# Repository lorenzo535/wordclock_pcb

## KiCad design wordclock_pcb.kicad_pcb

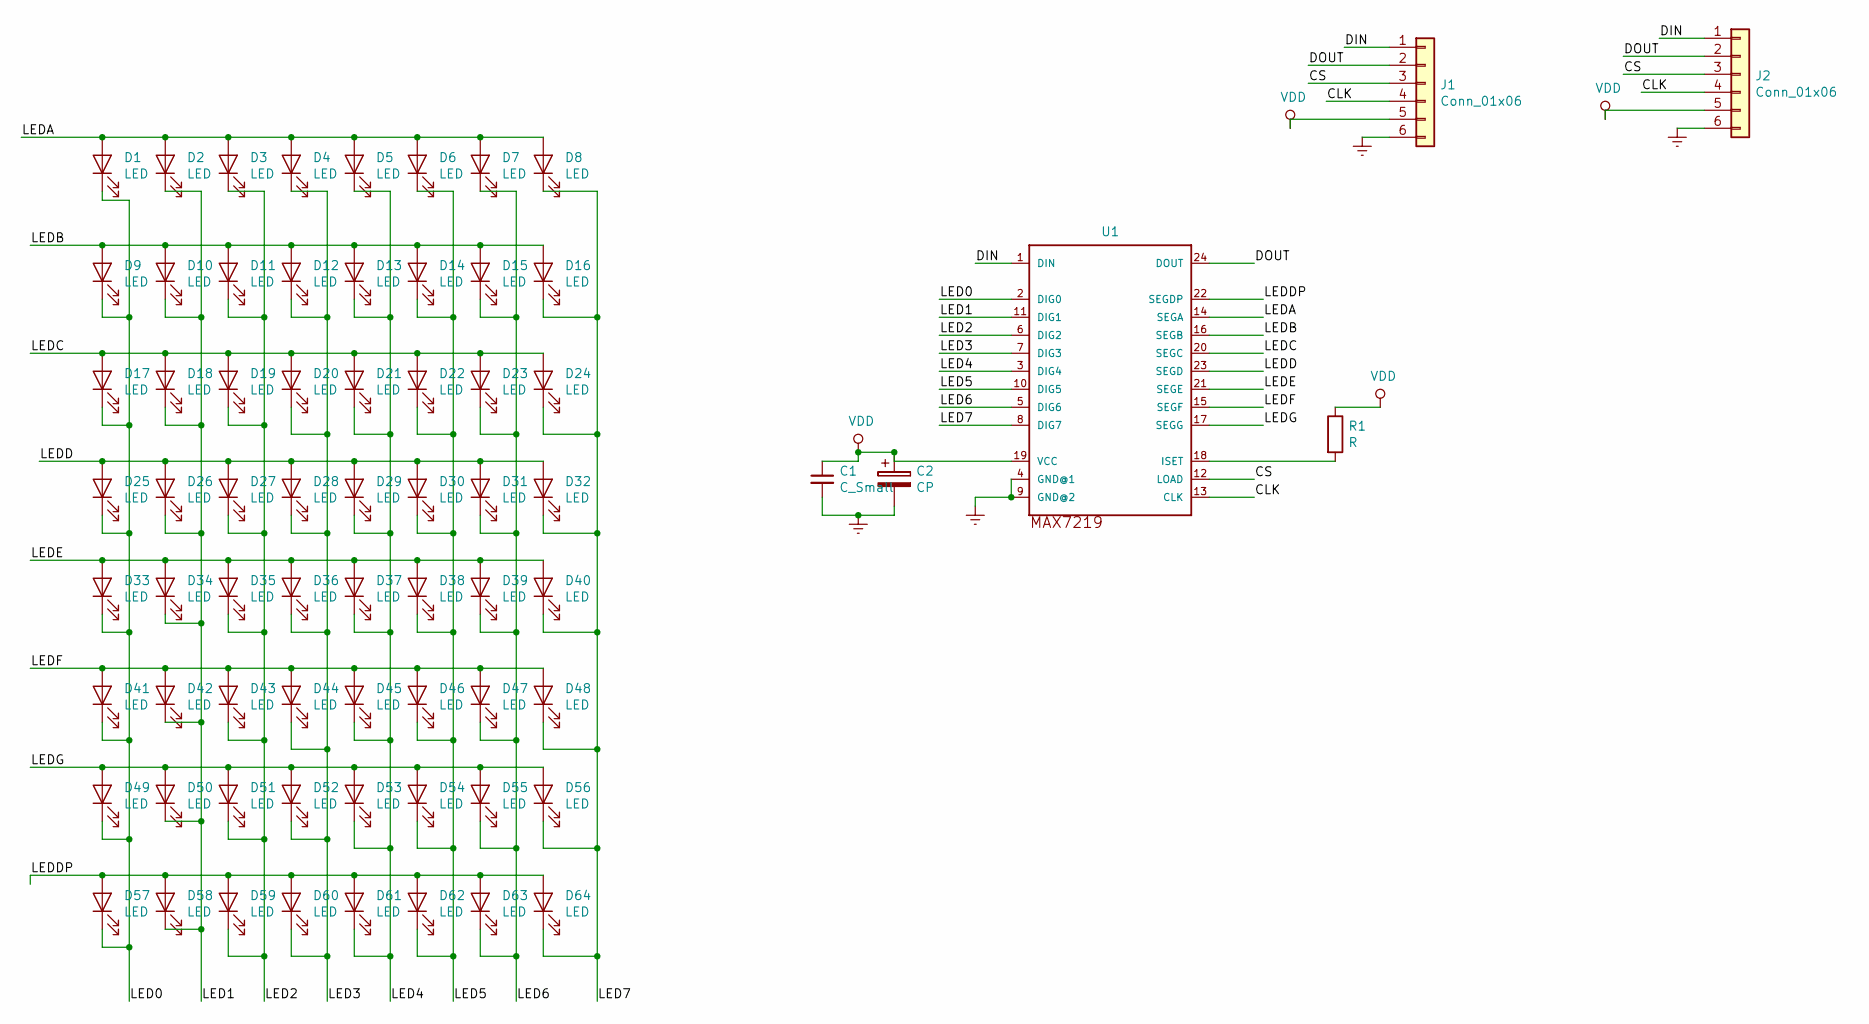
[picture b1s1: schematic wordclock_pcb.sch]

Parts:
C1: C_Small; CP_Radial_D4.0mm_P1.50mm
C2: CP; CP_Radial_D4.0mm_P1.50mm
D1, D2, D3, D4, D5, D6, D7, D8, D9, D10, D11, D12, D13, D14, D15, D16, D17, D18, D19, D20, D21, D22, D23, D24, D25, D26, D27, D28, D29, D30, D31, D32, D33, D34, D35, D36, D37, D38, D39, D40, D41, D42, D43, D44, D45, D46, D47, D48, D49, D50, D51, D52, D53, D54, D55, D56, D57, D58, D59, D60, D61, D62, D63, D64: LED; ledthroughhole
J1, J2: Conn_01x06; TerminalBlock_Phoenix_MPT-2.54mm_6pol
R1: R; R_Axial_DIN0207_L6.3mm_D2.5mm_P15.24mm_Horizontal
U1: MAX7219; DIL24

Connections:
/CLK: J1.4, J2.4, U1.13 (CLK)
/CS: J1.3, J2.3, U1.12 (LOAD)
/DIN: J1.1, J2.1, U1.1 (DIN)
/DOUT: J1.2, J2.2, U1.24 (DOUT)
/LED0: D1.1 (K), D9.1 (K), D17.1 (K), D25.1 (K), D33.1 (K), D41.1 (K), D49.1 (K), D57.1 (K), U1.2 (DIG0)
/LED1: D2.1 (K), D10.1 (K), D18.1 (K), D26.1 (K), D34.1 (K), D42.1 (K), D50.1 (K), D58.1 (K), U1.11 (DIG1)
/LED2: D3.1 (K), D11.1 (K), D19.1 (K), D27.1 (K), D35.1 (K), D43.1 (K), D51.1 (K), D59.1 (K), U1.6 (DIG2)
/LED3: D4.1 (K), D12.1 (K), D20.1 (K), D28.1 (K), D36.1 (K), D44.1 (K), D52.1 (K), D60.1 (K), U1.7 (DIG3)
/LED4: D5.1 (K), D13.1 (K), D21.1 (K), D29.1 (K), D37.1 (K), D45.1 (K), D53.1 (K), D61.1 (K), U1.3 (DIG4)
/LED5: D6.1 (K), D14.1 (K), D22.1 (K), D30.1 (K), D38.1 (K), D46.1 (K), D54.1 (K), D62.1 (K), U1.10 (DIG5)
/LED6: D7.1 (K), D15.1 (K), D23.1 (K), D31.1 (K), D39.1 (K), D47.1 (K), D55.1 (K), D63.1 (K), U1.5 (DIG6)
/LED7: D8.1 (K), D16.1 (K), D24.1 (K), D32.1 (K), D40.1 (K), D48.1 (K), D56.1 (K), D64.1 (K), U1.8 (DIG7)
/LEDA: D1.2 (A), D2.2 (A), D3.2 (A), D4.2 (A), D5.2 (A), D6.2 (A), D7.2 (A), D8.2 (A), U1.14 (SEGA)
/LEDB: D9.2 (A), D10.2 (A), D11.2 (A), D12.2 (A), D13.2 (A), D14.2 (A), D15.2 (A), D16.2 (A), U1.16 (SEGB)
/LEDC: D17.2 (A), D18.2 (A), D19.2 (A), D20.2 (A), D21.2 (A), D22.2 (A), D23.2 (A), D24.2 (A), U1.20 (SEGC)
/LEDD: D25.2 (A), D26.2 (A), D27.2 (A), D28.2 (A), D29.2 (A), D30.2 (A), D31.2 (A), D32.2 (A), U1.23 (SEGD)
/LEDDP: D57.2 (A), D58.2 (A), D59.2 (A), D60.2 (A), D61.2 (A), D62.2 (A), D63.2 (A), D64.2 (A), U1.22 (SEGDP)
/LEDE: D33.2 (A), D34.2 (A), D35.2 (A), D36.2 (A), D37.2 (A), D38.2 (A), D39.2 (A), D40.2 (A), U1.21 (SEGE)
/LEDF: D41.2 (A), D42.2 (A), D43.2 (A), D44.2 (A), D45.2 (A), D46.2 (A), D47.2 (A), D48.2 (A), U1.15 (SEGF)
/LEDG: D49.2 (A), D50.2 (A), D51.2 (A), D52.2 (A), D53.2 (A), D54.2 (A), D55.2 (A), D56.2 (A), U1.17 (SEGG)
Earth: C1.2, C2.2, J1.6, J2.6, U1.4 (GND@1), U1.9 (GND@2)
unnamed: R1.2, U1.18 (ISET)
VDD: C1.1, C2.1, J1.5, J2.5, R1.1, U1.19 (VCC)

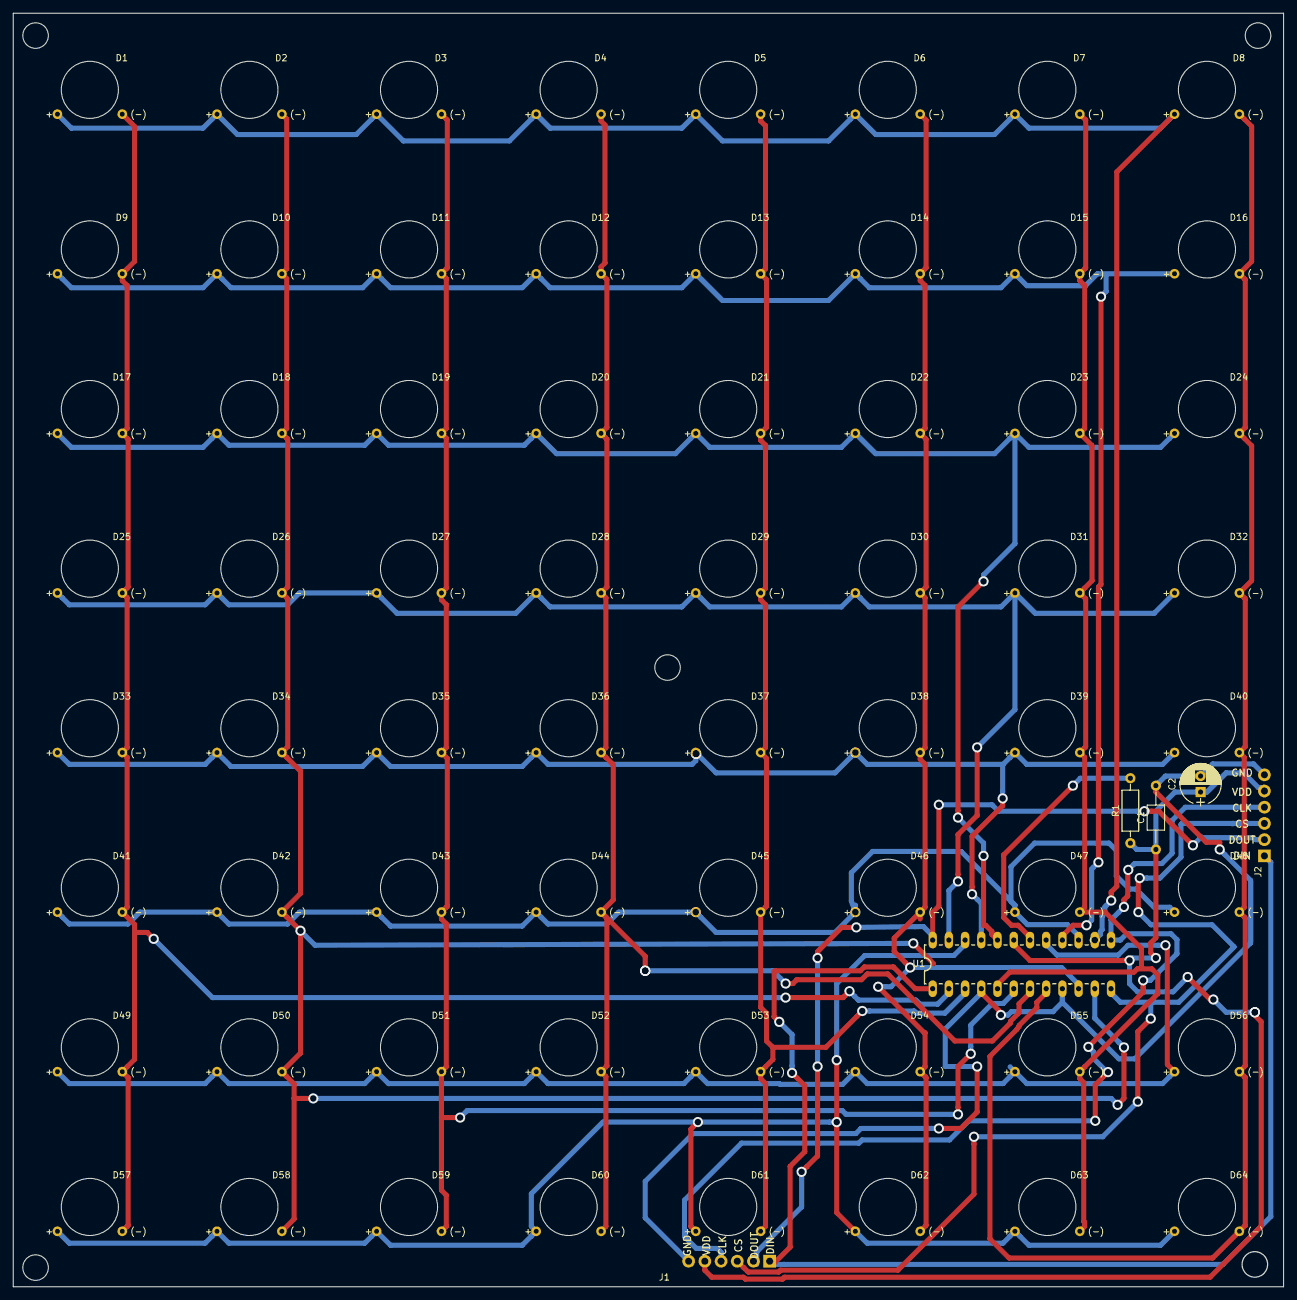
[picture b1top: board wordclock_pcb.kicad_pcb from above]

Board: 2 copper layers, 198.9 x 199.4 mm, 70 parts (0 on the bottom side), 23 nets.

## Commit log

2020-01-26 first version
2020-01-26 tweaks
